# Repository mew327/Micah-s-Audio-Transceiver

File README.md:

# Micah-s-Audio-Transceiver
Low Latency RF Transceiver

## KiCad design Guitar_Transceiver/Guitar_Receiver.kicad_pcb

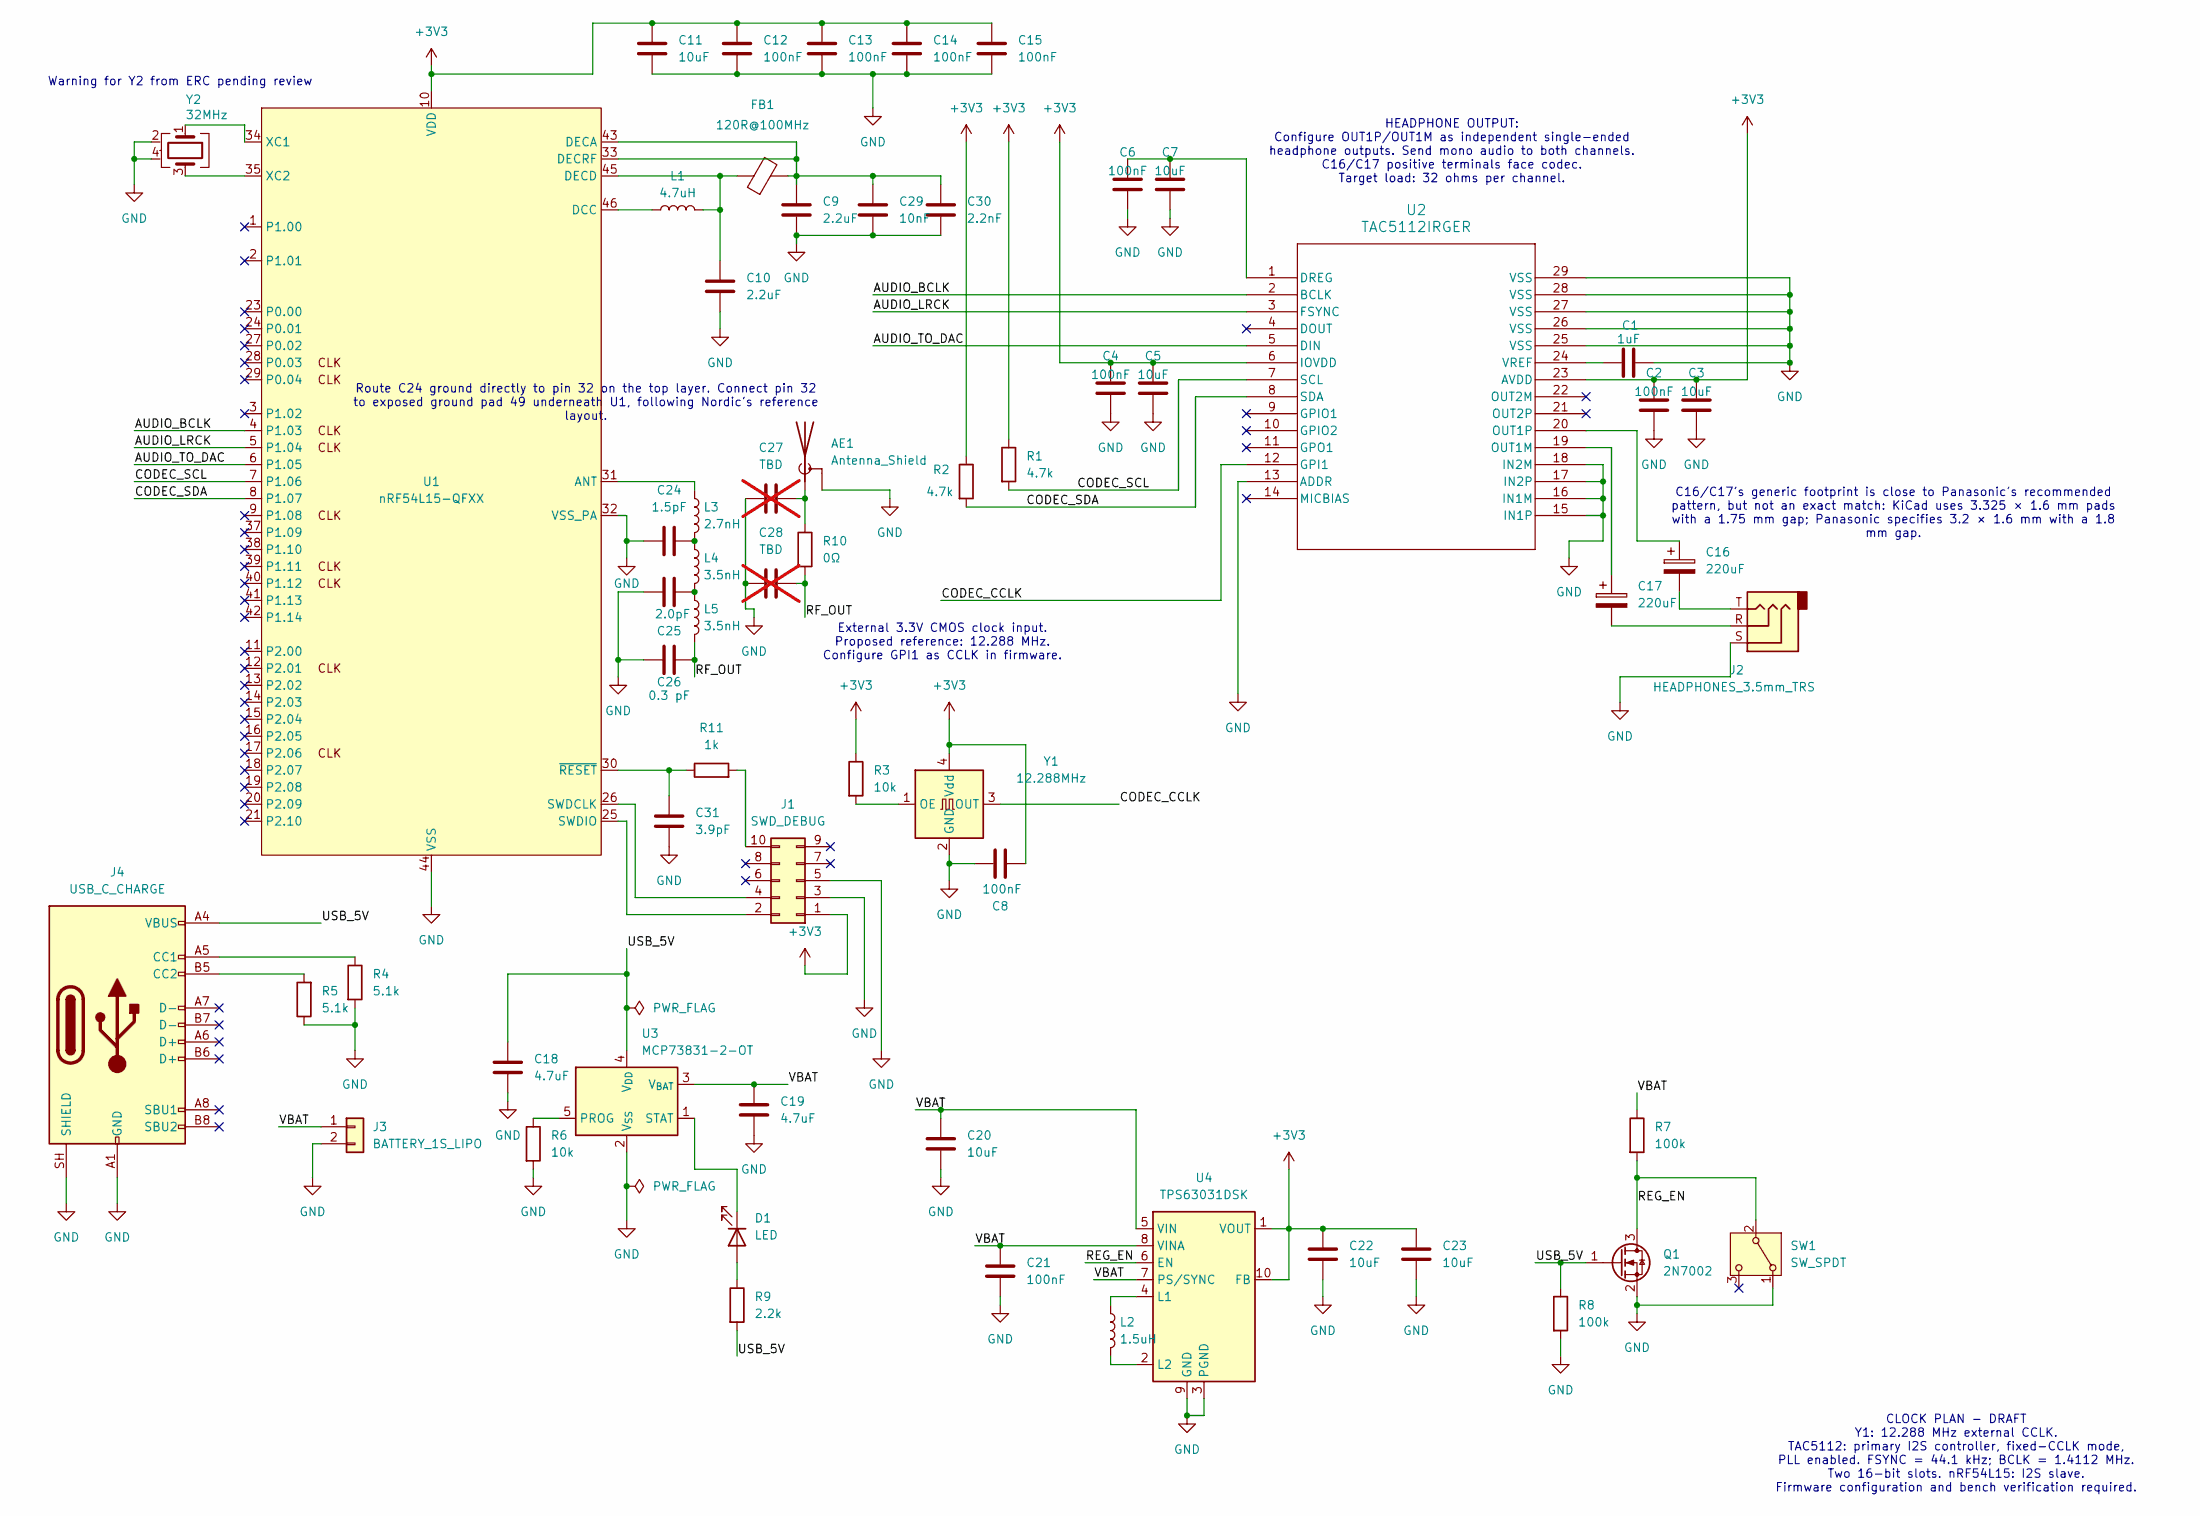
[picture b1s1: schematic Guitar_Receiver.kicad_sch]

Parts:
AE1: Antenna_Shield; IFA_SWRU120D_Copper_Draft
C1: 1uF; C_0603_1608Metric; Voltage Rating 10V
C2, C4, C6: 100nF; C_0603_1608Metric; Voltage Rating 10V
C3, C5, C7: 10uF; C_0805_2012Metric; Voltage Rating 10V
C8: 100nF; C_0603_1608Metric; Voltage Rating 10V; Tolerance ±10%
C9, C10: 2.2uF; C_0201_0603Metric; Voltage Rating 2.5V; Tolerance ±20%
C11: 10uF; C_0402_1005Metric; Voltage Rating 6.3V; Tolerance ±20%
C12, C13, C14, C15: 100nF; C_0201_0603Metric; Voltage Rating 6.3V; Tolerance ±10%
C16, C17: 220uF; C_Elec_6.3x5.8; Voltage Rating 6.3V; Tolerance ±20%; MPN EEEFP0J221AP
C18, C19: 4.7uF; C_0603_1608Metric; Voltage Rating 10V
C20, C22, C23: 10uF; C_0805_2012Metric; Voltage Rating 10 V
C21: 100nF; C_0603_1608Metric; Voltage Rating 10 V
C24: 1.5pF; C_0201_0603Metric; Tolerance ±0.05 pF; Voltage Rating ≥25 V
C25: 2.0pF; C_0201_0603Metric; Tolerance ±0.05 pF; Voltage Rating ≥25 V
C26: 0.3 pF; C_0201_0603Metric; Tolerance ±0.1 pF; Voltage Rating 50 V
C27, C28: TBD; C_0201_0603Metric; Voltage Rating ≥25 V; not fitted
C29: 10nF; C_0201_0603Metric; Tolerance ±10%; Voltage Rating ≥6.3 V
C30: 2.2nF; C_0201_0603Metric; Tolerance ±10%; Voltage Rating ≥10 V
C31: 3.9pF; C_0201_0603Metric; Tolerance ±0.25 pF; Voltage Rating 50 V
D1: LED; LED_0603_1608Metric; MPN APT1608SURCK
FB1: 120R@100MHz; L_0201_0603Metric; Current Rating 200 mA; MPN BLM03AG121SN1D
J1: SWD_DEBUG; PinHeader_2x05_P1.27mm_Vertical
J2: HEADPHONES_3.5mm_TRS; Jack_3.5mm_CUI_SJ1-3523N_Horizontal; MPN SJ1-3523N
J3: BATTERY_1S_LIPO; JST_PH_B2B-PH-K_1x02_P2.00mm_Vertical; MPN B2B-PH-K-S(LF)(SN)
J4: USB_C_CHARGE; USB_C_Receptacle_GCT_USB4105-xx-A_16P_TopMnt_Horizontal; MPN USB4105-GF-A
L1: 4.7uH; L_0603_1608Metric; Tolerance ±20%; Current Rating >120 mA
L2: 1.5uH; L_Coilcraft_LPS3015_3.0x3.0mm; Tolerance ±20%; MPN LPS3015-152MRC
L3: 2.7nH; L_0201_0603Metric; Tolerance ±0.1 nH; Current Rating ≥600 mA
L4, L5: 3.5nH; L_0201_0603Metric; Tolerance ±0.1 nH; Current Rating ≥500 mA
Q1: 2N7002; SOT-23
R1, R2: 4.7k; R_0603_1608Metric
R3, R6: 10k; R_0603_1608Metric
R4, R5: 5.1k; R_0603_1608Metric; Tolerance ±1%
R7, R8: 100k; R_0603_1608Metric
R9: 2.2k; R_0603_1608Metric
R10: 0Ω; R_0201_0603Metric
R11: 1k; R_0201_0603Metric
SW1: SW_SPDT; SW_SPDT_CK_JS102011SAQN; MPN JS102011SAQN
U1: nRF54L15-QFXX; QFN-48-1EP_6x6mm_P0.4mm_EP4.6x4.6mm_ThermalVias; MPN NRF54L15-QFAA-R
U2: TAC5112IRGER; TAC5112_RGE0024R_TI_Example_Candidate; MPN TAC5112IRGER
U3: MCP73831-2-OT; SOT-23-5
U4: TPS63031DSK; TPS63031_DSK0010A_TI_Example_Candidate
Y1: 12.288MHz; Oscillator_SMD_SiT_PQFN-4Pin_3.2x2.5mm; MPN SiT8008BC-22-33E-12.288000G
Y2: 32MHz; Crystal_SMD_2016-4Pin_2.0x1.6mm; MPN CX2016DB32000D0FLJCC

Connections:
+3V3: C2.1, C3.1, C4.1, C5.1, C8.2, C11.1, C12.1, C13.1, C14.1, C15.1, C22.1, C23.1, J1.1, R1.1, R2.1, R3.1, U1.10 (VDD), U1.22 (VDD), U1.36 (VDD), U1.47 (VDD), U1.48 (VDD), U2.6 (IOVDD), U2.23 (AVDD), U4.1 (VOUT), U4.10 (FB), Y1.4 (Vdd)
/AUDIO_BCLK: U1.4 (P1.03), U2.2 (BCLK)
/AUDIO_LRCK: U1.5 (P1.04), U2.3 (FSYNC)
/AUDIO_TO_DAC: U1.6 (P1.05), U2.5 (DIN)
/CODEC_CCLK: U2.12 (GPI1), Y1.3 (OUT)
/CODEC_SCL: R1.2, U1.7 (P1.06), U2.7 (SCL)
/CODEC_SDA: R2.2, U1.8 (P1.07), U2.8 (SDA)
/REG_EN: Q1.3 (D), R7.2, SW1.2 (B), U4.6 (EN)
/RF_OUT: C26.2, C28.2, L5.2, R10.2
/USB_5V: C18.2, J4.A4 (VBUS), J4.A9 (VBUS), J4.B4 (VBUS), J4.B9 (VBUS), Q1.1 (G), R8.1, R9.2, U3.4 (V_{DD})
/VBAT: C19.2, C20.1, C21.1, J3.1, R7.1, U3.3 (V_{BAT}), U4.5 (VIN), U4.7 (PS/SYNC), U4.8 (VINA)
GND: AE1.2 (Shield), C1.2, C2.2, C3.2, C4.2, C5.2, C6.2, C7.2, C8.1, C9.2, C10.2, C11.2, C12.2, C13.2, C14.2, C15.2, C18.1, C19.1, C20.2, C21.2, C22.2, C23.2, C24.1, C25.1, C26.1, C27.1, C28.1, C29.2, C30.2, C31.2, J1.3, J1.5, J2.S, J3.2, J4.A1 (GND), J4.A12 (GND), J4.B1 (GND), J4.B12 (GND), J4.SH (SHIELD), Q1.2 (S), R4.2, R5.1, R6.2, R8.2, SW1.1 (A), U1.32 (VSS_PA), U1.44 (VSS), U1.49 (VSS), U2.13 (ADDR), U2.15 (IN1P), U2.16 (IN1M), U2.17 (IN2P), U2.18 (IN2M), U2.25 (VSS), U2.26 (VSS), U2.27 (VSS), U2.28 (VSS), U2.29 (VSS), U3.2 (V_{SS}), U4.3 (PGND), U4.9 (GND), U4.11 (PGND), Y1.2 (GND), Y2.2 (G), Y2.4 (G)
unnamed: AE1.1 (A), C27.2, R10.1
unnamed: C16.2, J2.T
unnamed: C17.2, J2.R
unnamed: C24.2, L3.2, L4.1
unnamed: C25.2, L4.2, L5.1
unnamed: D1.2 (A), R9.1
unnamed: D1.1 (K), U3.1 (STAT)
unnamed: J1.2, U1.25 (SWDIO)
unnamed: J1.4, U1.26 (SWDCLK)
unnamed: J1.10, R11.2
unnamed: J4.A5 (CC1), R4.1
unnamed: J4.B5 (CC2), R5.2
unnamed: L3.1, U1.31 (ANT)
unnamed: L1.1, U1.46 (DCC)
unnamed: C9.1, C29.1, C30.1, FB1.2, U1.33 (DECRF), U1.43 (DECA)
unnamed: C10.1, FB1.1, L1.2, U1.45 (DECD)
unnamed: U1.34 (XC1), Y2.1
unnamed: U1.35 (XC2), Y2.3
unnamed: C31.1, R11.1, U1.30 (~RESET)
unnamed: C6.1, C7.1, U2.1 (DREG)
unnamed: C17.1, U2.19 (OUT1M)
unnamed: C16.1, U2.20 (OUT1P)
unnamed: C1.1, U2.24 (VREF)
unnamed: R6.1, U3.5 (PROG)
unnamed: L2.1, U4.4 (L1)
unnamed: L2.2, U4.2 (L2)
unnamed: R3.2, Y1.1 (OE)

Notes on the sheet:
HEADPHONE OUTPUT: Configure OUT1P/OUT1M as independent single-ended headphone outputs. Send mono audio to both channels. C16/C17 positive terminals face codec. Target load: 32 ohms per channel.
External 3.3V CMOS clock input. Proposed reference: 12.288 MHz. Configure GPI1 as CCLK in firmware.
CLOCK PLAN - DRAFT Y1: 12.288 MHz external CCLK. TAC5112: primary I2S controller, fixed-CCLK mode, PLL enabled. FSYNC = 44.1 kHz; BCLK = 1.4112 MHz. Two 16-bit slots. nRF54L15: I2S slave. Firmware configuration and bench verification required.
C16/C17's generic footprint is close to Panasonic's recommended pattern, but not an exact match: KiCad uses 3.325 × 1.6 mm pads with a 1.75 mm gap; Panasonic specifies 3.2 × 1.6 mm with a 1.8 mm gap.
Route C24 ground directly to pin 32 on the top layer. Connect pin 32 to exposed ground pad 49 underneath U1, following Nordic's reference layout.
Warning for Y2 from ERC pending review

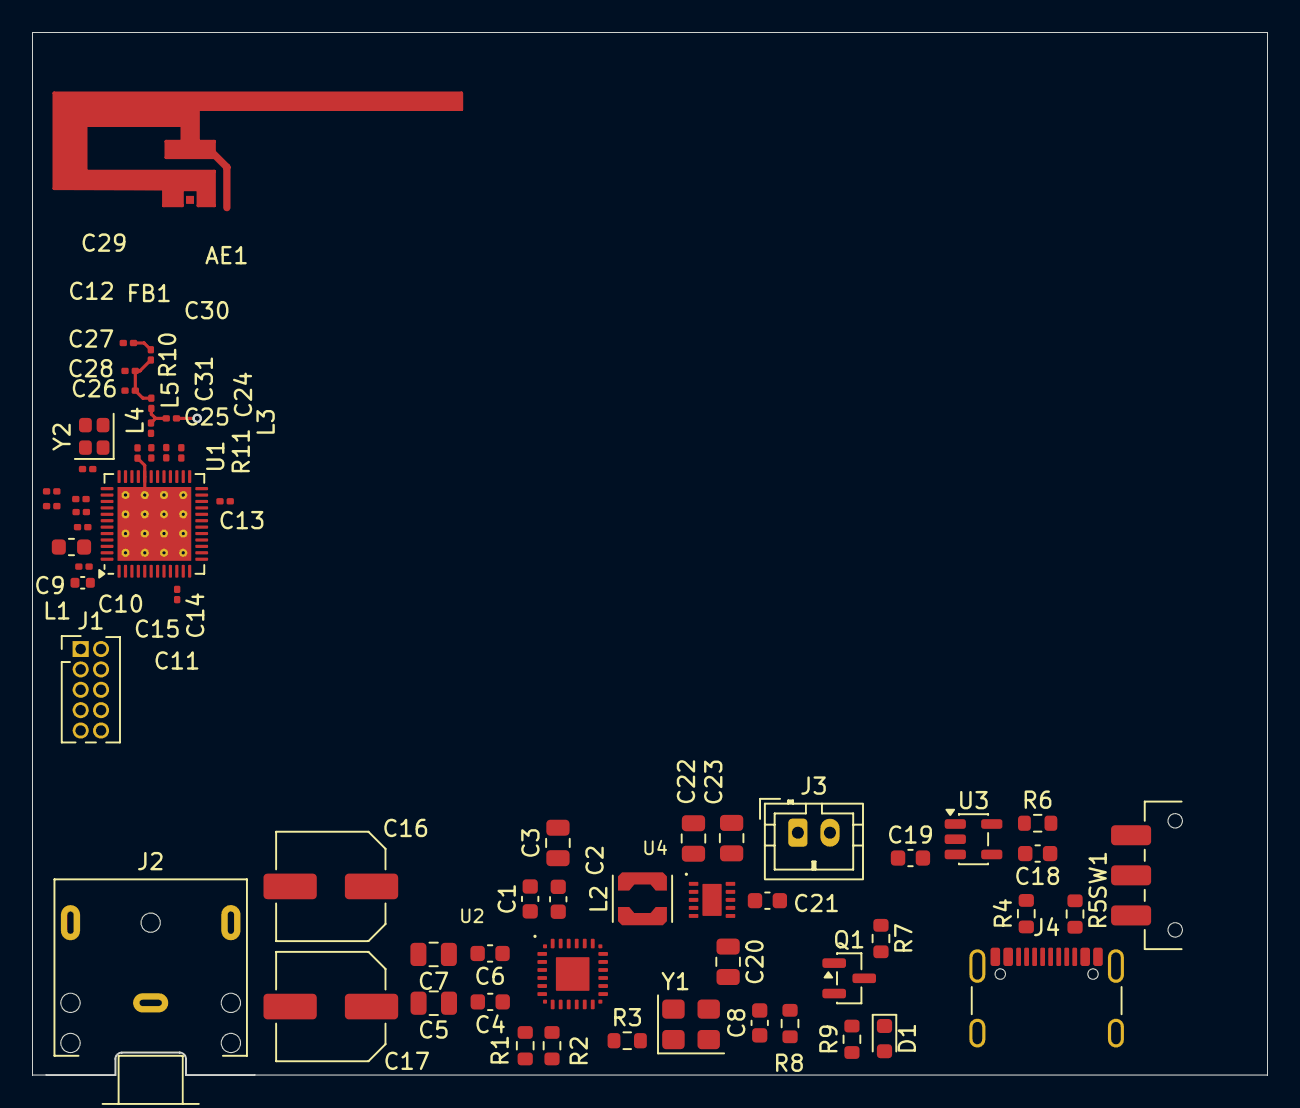
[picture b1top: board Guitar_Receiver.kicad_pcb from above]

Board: 4 copper layers, 77.0 x 65.0 mm, 62 parts (0 on the bottom side), 39 nets.
